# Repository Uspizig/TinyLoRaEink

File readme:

This is a repo for a Tiny LoRA Node.
Here it is described a small Addon Board for a Lilygo Mini EPaper Core 1.02" Inch Display

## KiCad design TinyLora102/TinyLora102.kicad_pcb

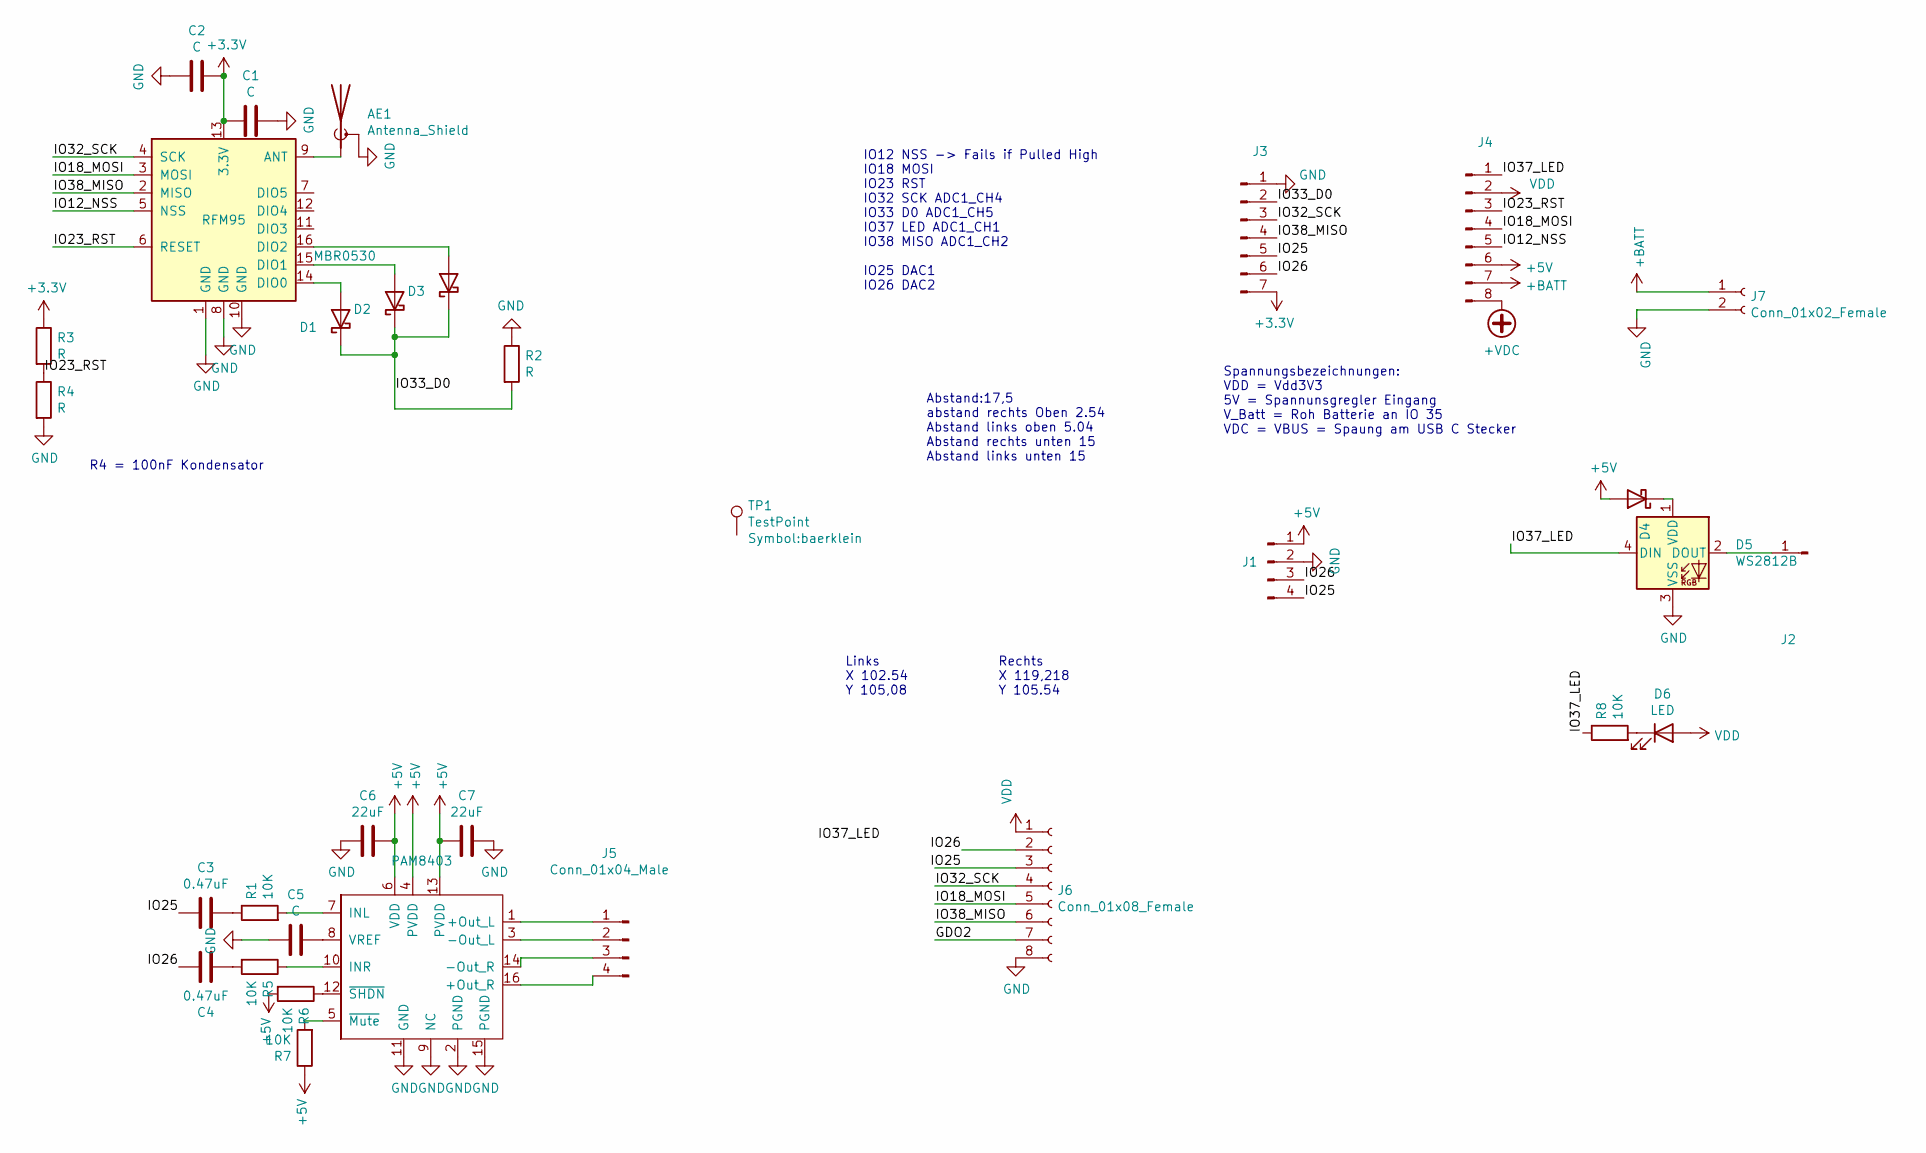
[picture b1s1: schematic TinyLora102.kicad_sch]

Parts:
AE1: Antenna_Shield; SMA_Samtec_SMA-J-P-H-ST-EM1_EdgeMount
C1, C2, C5: C; C_0805_2012Metric_Pad1.15x1.40mm_HandSolder
C3, C4: 0.47uF; C_0805_2012Metric_Pad1.15x1.40mm_HandSolder
C6, C7: 22uF; C_0805_2012Metric_Pad1.15x1.40mm_HandSolder
D1, D2, D3, D4: MBR0530; D_SOD-123
D5: WS2812B; LED_WS2812B_PLCC4_5.0x5.0mm_P3.2mm
D6: LED; LED_0805_2012Metric_Pad1.15x1.40mm_HandSolder
J1, J5: Conn_01x04_Male; PinHeader_1x04_P2.54mm_Vertical
J2: Conn_01x01_Male; TestPoint_Pad_2.5x2.5mm
J3: Conn_01x07_Male; PinHeader_1x07_P2.54mm_Vertical_SMD_Pin1Left
J4: Conn_01x08_Male; PinHeader_1x08_P2.54mm_Vertical_SMD_Pin1Left
J6: Conn_01x08_Female; PinHeader_1x08_P1.27mm_Vertical
J7: Conn_01x02_Female; JST_GH_SM02B-GHS-TB_1x02-1MP_P1.25mm_Horizontal
PAM8403: PAM8403; SOP-16_4.55x10.3mm_P1.27mm
R1, R5, R6, R7, R8: 10K; R_0805_2012Metric_Pad1.15x1.40mm_HandSolder
R2, R3, R4: R; R_0805_2012Metric_Pad1.15x1.40mm_HandSolder
RFM95: RFM95W-868S2; HOPERF_RFM9XW_SMD_3D
TP1: TestPoint; baerklein

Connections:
+3V3: C1.2, C2.1, J3.7, R3.1, RFM95.13 (3.3V)
+5V: C6.1, C7.2, D4.2 (A), J1.1, J4.6, PAM8403.4 (PVDD), PAM8403.6 (VDD), PAM8403.13 (PVDD), R6.2, R7.1
+BATT: J4.7, J7.1; also elsewhere on the board
+VDC: J4.8
/GDO2: J6.7
/IO12_NSS: J4.5, RFM95.5 (NSS)
/IO18_MOSI: J4.4, J6.5, RFM95.3 (MOSI)
/IO23_RST: J4.3, R3.2, R4.1, RFM95.6 (RESET)
/IO25: C3.2, J1.4, J3.5, J6.3
/IO26: C4.1, J1.3, J3.6, J6.2
/IO32_SCK: J3.3, J6.4, RFM95.4 (SCK)
/IO33_D0: D1.1 (K), D2.1 (K), D3.1 (K), J3.2, R2.2
/IO37_LED: D5.4 (DIN), J4.1, R8.1
/IO38_MISO: J3.4, J6.6, RFM95.2 (MISO)
GND: AE1.2 (Shield), C1.1, C2.2, C5.2, C6.2, C7.1, D5.3 (VSS), J1.2, J3.1, J6.8, J7.2, PAM8403.2 (PGND), PAM8403.9 (NC), PAM8403.11 (GND), PAM8403.15 (PGND), R2.1, R4.2, RFM95.1 (GND), RFM95.8 (GND), RFM95.10 (GND); also elsewhere on the board
unnamed: AE1.1 (A), RFM95.9 (ANT)
unnamed: C3.1, R1.1
unnamed: C4.2, R5.2
unnamed: C5.1, PAM8403.8 (VREF)
unnamed: D1.2 (A), RFM95.14 (DIO0)
unnamed: D2.2 (A), RFM95.15 (DIO1)
unnamed: D3.2 (A), RFM95.16 (DIO2)
unnamed: D4.1 (K), D5.1 (VDD)
unnamed: D5.2 (DOUT), J2.1
unnamed: D6.1 (K), R8.2
unnamed: J5.1, PAM8403.1 (+Out_L)
unnamed: J5.2, PAM8403.3 (-Out_L)
unnamed: J5.3, PAM8403.14 (-Out_R)
unnamed: J5.4, PAM8403.16 (+Out_R)
unnamed: PAM8403.5 (~Mute), R7.2
unnamed: PAM8403.7 (INL), R1.2
unnamed: PAM8403.10 (INR), R5.1
unnamed: PAM8403.12 (~SHDN), R6.1
VDD: D6.2 (A), J4.2, J6.1

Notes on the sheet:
Spannungsbezeichnungen: VDD = Vdd3V3 5V = Spannunsgregler Eingang V_Batt = Roh Batterie an IO 35 VDC = VBUS = Spaung am USB C Stecker
Abstand:17,5 abstand rechts Oben 2.54 Abstand links oben 5.04 Abstand rechts unten 15 Abstand links unten 15
Rechts X 119,218 Y 105.54
Links X 102.54 Y 105,08
IO12 NSS -> Fails if Pulled High IO18 MOSI IO23 RST IO32 SCK ADC1_CH4 IO33 D0 ADC1_CH5 IO37 LED ADC1_CH1 IO38 MISO ADC1_CH2 IO25 DAC1 IO26 DAC2
R4 = 100nF Kondensator

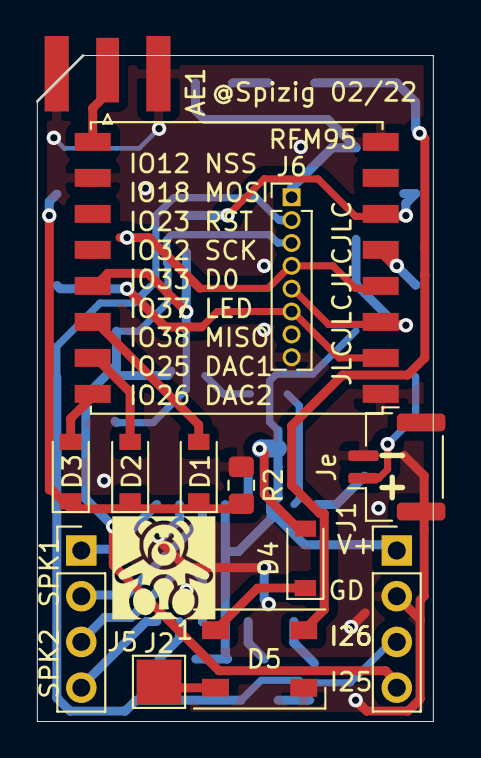
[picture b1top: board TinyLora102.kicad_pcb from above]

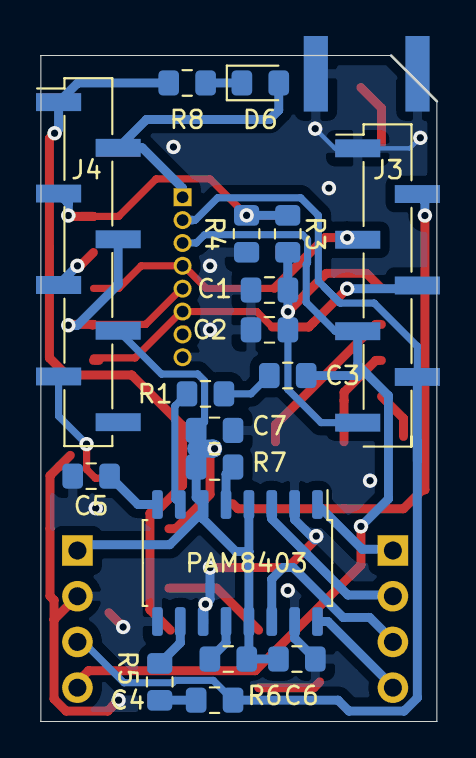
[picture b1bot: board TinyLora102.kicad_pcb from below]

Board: 2 copper layers, 22.0 x 37.0 mm, 32 parts (18 on the bottom side), 32 nets.

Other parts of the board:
Je: Conn_01x02_Female; JST_GH_SM02B-GHS-TB_1x02-1MP_P1.25mm_Horizontal

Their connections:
+BATT: Je.1; also elsewhere on the board
GND: Je.2; also elsewhere on the board

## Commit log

2024-04-21 Rename readme to readme.md
